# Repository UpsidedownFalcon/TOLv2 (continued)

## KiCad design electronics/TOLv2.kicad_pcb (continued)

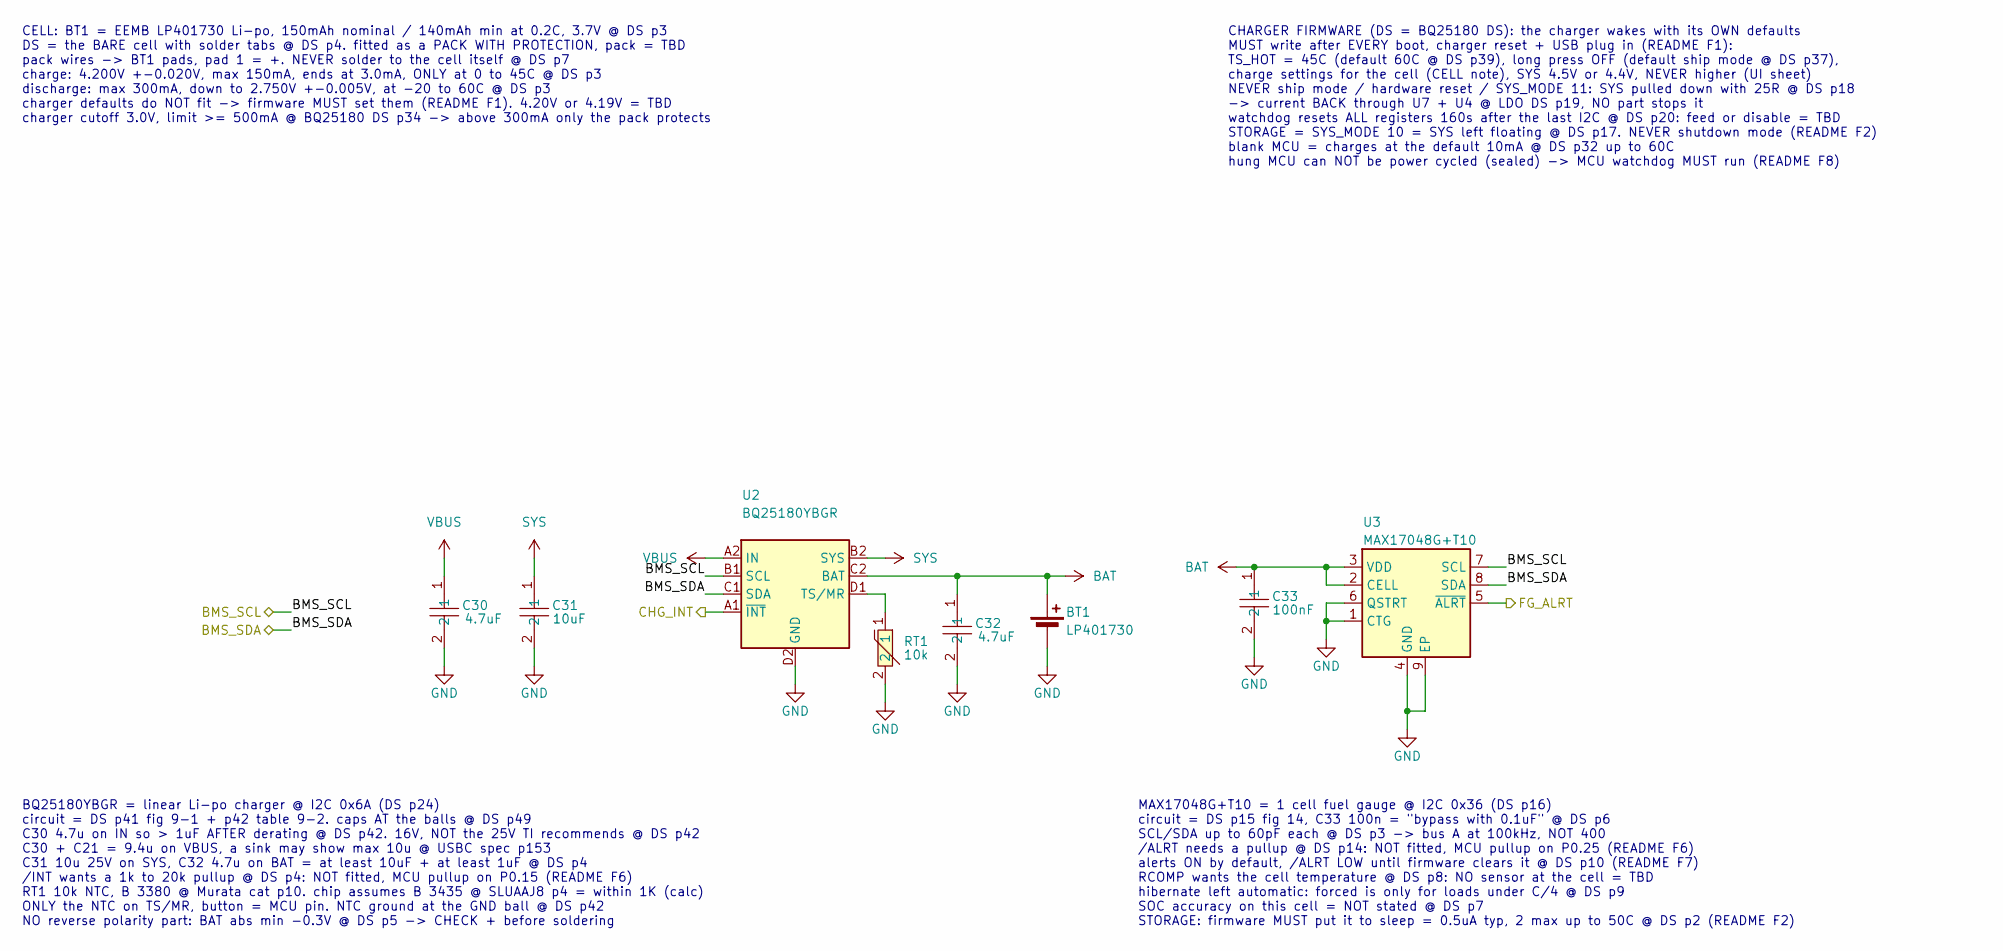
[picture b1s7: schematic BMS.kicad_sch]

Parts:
BT1: LP401730; BAT_LIPO_150mAh_LP401730; MPN LP401730
C30, C32: 4.7uF; CAP_4u7_16V_X5R_0603_CL10A475KO8NNNC; Tolerance +-10%; Voltage 16V; MPN CL10A475KO8NNNC; LCSC Part # C19666
C31: 10uF; CAP_10uF_25V_X5R_0603_CL10A106MA8NRNC; Tolerance +-20%; Voltage 25V; MPN CL10A106MA8NRNC; LCSC Part # C96446
C33: 100nF; CAP_100nF_16V_X7R_0402_CL05B104KO5NNNC; Tolerance +-10%; Voltage 16V; MPN CL05B104KO5NNNC; LCSC Part # C1525
RT1: 10k; NTC_10k_0402_NCP15XH103F03RC; Tolerance +-1%; MPN NCP15XH103F03RC; LCSC Part # C77131
U2: BQ25180YBGR; CHG_BQ25180YBGR; MPN BQ25180YBGR; LCSC Part # C3682423
U3: MAX17048G+T10; FG_MAX17048G-T10; MPN MAX17048G+T10; LCSC Part # C2682616

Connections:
/BMS/BMS_SCL: U2.B1 (SCL), U3.7 (SCL); also elsewhere on the board
/BMS/BMS_SDA: U2.C1 (SDA), U3.8 (SDA); also elsewhere on the board
/BMS/CHG_INT: U2.A1 (~INT); also elsewhere on the board
/BMS/FG_ALRT: U3.5 (~ALRT); also elsewhere on the board
BAT: BT1.1 (+), C32.1, C33.1, U2.C2 (BAT), U3.2 (CELL), U3.3 (VDD); also elsewhere on the board
GND: BT1.2 (-), C30.2, C31.2, C32.2, C33.2, RT1.2, U2.D2 (GND), U3.1 (CTG), U3.4 (GND), U3.6 (QSTRT), U3.9 (EP); also elsewhere on the board
unnamed: RT1.1, U2.D1 (TS/MR)
SYS: C31.1, U2.B2 (SYS); also elsewhere on the board
VBUS: C30.1, U2.A2 (IN); also elsewhere on the board

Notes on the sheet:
CELL: BT1 = EEMB LP401730 Li-po, 150mAh nominal / 140mAh min at 0.2C, 3.7V @ DS p3 DS = the BARE cell with solder tabs @ DS p4. fitted as a PACK WITH PROTECTION, pack = TBD pack wires -> BT1 pads, pad 1 = +. NEVER solder to the cell itself @ DS p7 charge: 4.200V +-0.020V, max 150mA, ends at 3.0mA, 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
BQ25180YBGR = linear Li-po charger @ I2C 0x6A (DS p24) circuit = DS p41 fig 9-1 + p42 table 9-2. caps AT the balls @ DS p49 C30 4.7u on IN so > 1uF AFTER derating @ DS p42. 16V, NOT the 25V TI recommends @ DS p42 C30 + C21 = 9.4u on VBUS, a sink may show max 10u @ USBC spec p153 C31 10u 25V on SYS,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
CHARGER FIRMWARE (DS = BQ25180 DS): the charger wakes with its OWN defaults MUST write after EVERY boot, charger reset + USB plug in (README F1): TS_HOT = 45C (default 60C @ DS p39), long press OFF (default ship mode @ DS p37), charge settings for the cell (CELL note), SYS 4.5V or 4.4V, NEVER highe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
MAX17048G+T10 = 1 cell fuel gauge @ I2C 0x36 (DS p16) circuit = DS p15 fig 14, C33 100n = "bypass with 0.1uF" @ DS p6 SCL/SDA up to 60pF each @ DS p3 -> bus A at 100kHz, NOT 400 /ALRT needs a pullup @ DS p14: NOT fitted, MCU pullup on P0.25 (README F6) alerts ON by default, /ALRT LOW until firmware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

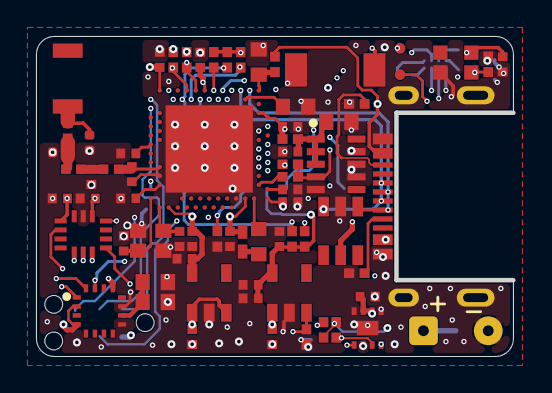
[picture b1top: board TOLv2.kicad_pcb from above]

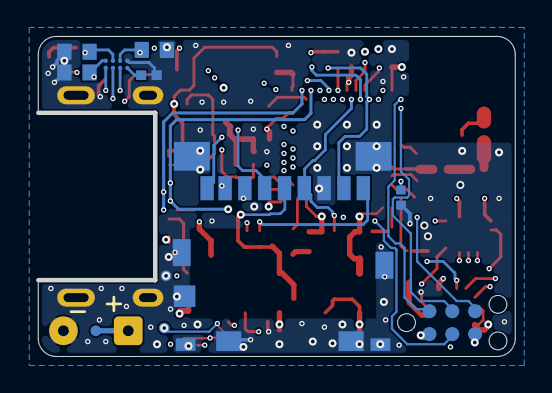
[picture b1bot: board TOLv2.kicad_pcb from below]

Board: 6 copper layers, 26.5 x 17.8 mm, 81 parts (11 on the bottom side), 56 nets.

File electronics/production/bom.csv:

Designator,Footprint,Quantity,Value,LCSC Part #
ANT1,ANT_RFANT3216120A5T,1,RFANT3216120A5T,C127629
"C1, C2",CAP_16pF_50V_NP0_0402_CC0402GRNPO9BN160,2,16pF,C513591
C11,CAP_100pF_50V_C0G_0402_0402CG101J500NT,1,100pF,C1546
"C12, C23, C33, C36, C37, C41, C42, C5, C7, C8",CAP_100nF_16V_X7R_0402_CL05B104KO5NNNC,10,100nF,C1525
"C14, C15, C34, C35, C38, C46, C6",CAP_1uF_25V_X5R_0402_CL05A105KA5NQNC,7,1uF,C52923
C16,CAP_47nF_25V_X7R_0402_TCC0402X7R473K250AT,1,47nF,C466239
"C20, C21, C30, C32, C47",CAP_4u7_16V_X5R_0603_CL10A475KO8NNNC,5,4.7uF,C19666
C3,CAP_1pF_50V_NP0_0402_CC0402BRNPO9BN1R0,1,1pF,C309455
"C31, C39, C43",CAP_10uF_25V_X5R_0603_CL10A106MA8NRNC,3,10uF,C96446
C4,CAP_1p2_50V_C0G_0402_0402CG1R2B500NT,1,1.2pF,C575437
C40,CAP_10uF_6V3_X5R_0402_CL05A106MQ5NUNC,1,10uF,C15525
C9,CAP_820pF_50V_C0G_0402_0402CG821J500NT,1,820pF,C913875
D1,ESD_AOZ8904CIL,1,AOZ8904CIL,C2649893
D2,LED_WS2812B-2020-V6,1,WS2812B-2020-V6,C52917434
J1,CONN_USBC16_TYPE-C-16P-CB1p6-073,1,TYPE-C 16P CB1.6 073,C2906290
J2,CONN_MICROSD_TF-110,1,TF-110,C266613
L1,IND_4n7_0402_VHF100505HQ4N7BT,1,4.7nH,C3032786
L2,IND_10uH_0603_MYH1608N100MT,1,10uH,C55079856
L3,IND_15nH_0402_VHF100505H15NKT,1,15nH,C381880
L5,IND_2n2_0402_TCGL1005B2N2BAT,1,2.2nH,C52109817
L6,IND_6n8_0402_TCGL1005B6N8JAT,1,6.8nH,C52109831
R1,RES_100R_0402_0402WGF1000TCE,1,100R,C25076
"R12, R13, R14, R15, R16, R19, R21, R22, R6, R7, R9",RES_10k_0402_0402WGF1002TCE,11,10k,C25744
"R2, R3, R4",RES_5k1_0402_0402WGF5101TCE,3,5.1k,C25905
R20,RES_1M_0402_0402WGF1004TCE,1,1M,C26083
R24,RES_1k_0402_0402WGF1001TCE,1,1k,C11702
R5,RES_2R2_0402_SCR0402F2R2,1,2.2R,C3015708
RT1,NTC_10k_0402_NCP15XH103F03RC,1,10k,C77131
SW1,SW_TS-1088-AR02016,1,TS-1088-AR02016,C720477
U1,MCU_NRF52840-QIAA-R,1,NRF52840-QIAA-R,C190794
U2,CHG_BQ25180YBGR,1,BQ25180YBGR,C3682423
U3,FG_MAX17048G-T10,1,MAX17048G+T10,C2682616
"U4, U7",LDO_3V0_TPS7A0230PDBVR,2,TPS7A0230PDBVR,C3747031
U5,IMU_ICM-45686,1,ICM-45686,C22459454
U6,MAG_MMC5983MA,1,MMC5983MA,C404329
X1,XTAL_32MHz_2016_NX2016SA-32M-EXS00A-CS06465,1,32MHz,C1986260
Y1,TCXO_32k768_TG-3541CE,1,TG-3541CE 32.7680KXA3,C1987384
